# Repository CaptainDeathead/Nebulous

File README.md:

# Nebulous

Nebulous is a retro console system powered by a Raspberry Pi. Designed for both nostalgia and innovation, it offers a unique blend of custom hardware and software to deliver an exciting multiplayer gaming experience.

## Features

- **Custom Controllers**: Nebulous supports up to 4 controllers for multiplayer gaming.
- **SD Card Cartridges**: Games are loaded via SD card cartridges, offering a retro game-swapping experience.
- **3D Printed Shell**: The physical console is encased in a sleek and durable 3D-printed shell.
- **Custom Games**: Includes a variety of games designed specifically for Nebulous (see the list below).
- **NES Game Support**: Play classic `.nes` files for old NES games.

## Custom Games

The `games` directory contains the following games created specifically for Nebulous using Pygame:

- **Caliby**: A calibration tool for testing controllers with the Nebulous.
- **Meteors**: A 4-player Asteroids clone.
- **Pong**: The classic Pong game.
- **Shape Royale**: A class-based battle royale where you play as 2D shapes.
- **Snither**: A multiplayer merge of Slither.io and classic Snake.
- **Tetris**: A 4-player version of the timeless Tetris game.

## Design Files

All files related to the physical design of Nebulous are located in the `/design` directory, including:

- **3D Printing Files**: Models for the Nebulous shell.
- **Controller PCB Designs**: Schematics and layouts for custom controllers.
- **Wiring Designs**: Diagrams and plans for wiring the console, controllers, and other components.

## How It Works

- **Without Cartridge**: If no game cartridge is inserted, the console will prompt you to insert one.
- **With Cartridge**: When a cartridge is inserted, the console attempts to load and play the game.

## Getting Started

1. **Hardware Setup**:
   - Assemble the 3D-printed case using files from the `/design` directory.
   - Connect up to 4 custom controllers using the provided PCB and wiring designs.
   - Insert an SD card cartridge containing your desired game.

2. **Software Setup**:
   - Clone the repository:
     ```bash
     git clone https://github.com/CaptainDeathead/Nebulous.git
     ```
   - Navigate to the `rpi-install` directory and run the `install.sh` script to set up the console:
     ```bash
     cd Nebulous/rpi-install
     ./install.sh
     ```

3. **Running Games**:
   - Insert a game cartridge to start playing.
   - Alternatively, load a `.nes` file for older NES games.

## Contributing

Contributions are welcome! Feel free to submit pull requests or open issues for bug reports and feature suggestions.

## License

This project is licensed under the MIT License - see the [LICENSE](LICENSE) file for details.

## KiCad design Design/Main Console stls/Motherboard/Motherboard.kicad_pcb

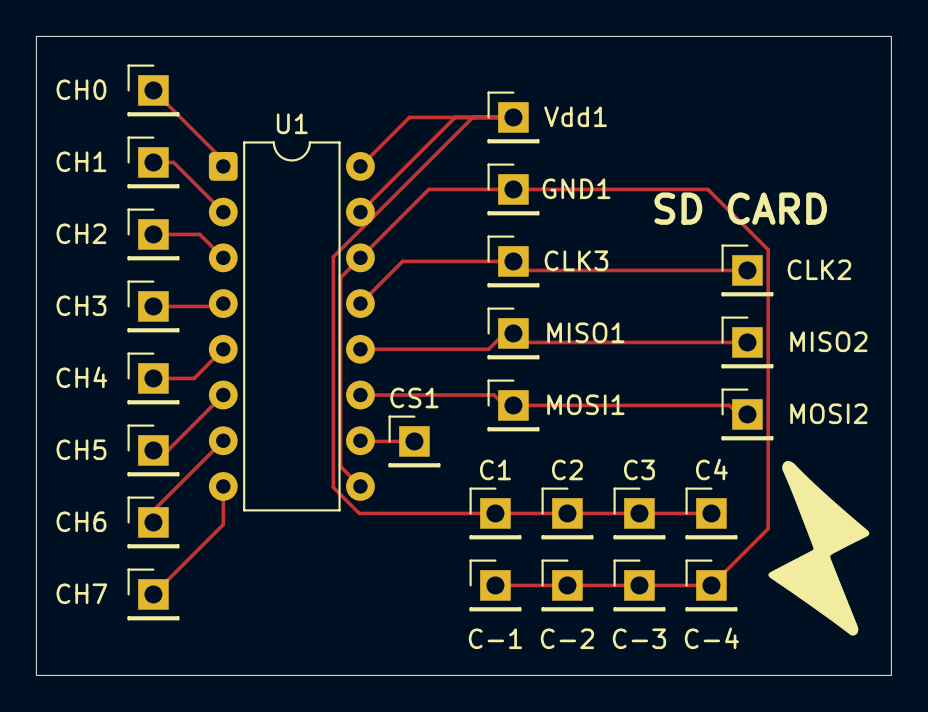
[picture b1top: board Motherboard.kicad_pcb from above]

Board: 2 copper layers, 47.5 x 35.5 mm, 26 parts (0 on the bottom side), 14 nets.

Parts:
C1, C2, C3, C4: TestPoint; PinHeader_1x01_P2.54mm_Vertical
C-1, C-2, C-3, C-4: TestPoint; PinHeader_1x01_P2.54mm_Vertical
CH0, CH1, CH2, CH3, CH4, CH5, CH6, CH7: TestPoint; PinHeader_1x01_P2.54mm_Vertical
CLK2, CLK3: TestPoint; PinHeader_1x01_P2.54mm_Vertical
CS1: TestPoint; PinHeader_1x01_P2.54mm_Vertical
GND1: TestPoint; PinHeader_1x01_P2.54mm_Vertical
MISO1, MISO2: TestPoint; PinHeader_1x01_P2.54mm_Vertical
MOSI1, MOSI2: TestPoint; PinHeader_1x01_P2.54mm_Vertical
U1: MCP3008; DIP-16_W7.62mm
Vdd1: TestPoint; PinHeader_1x01_P2.54mm_Vertical

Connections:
unnamed: C-1.1, C-2.1, C-3.1, C-4.1, GND1.1, U1.9 (DGND), U1.14 (AGND)
unnamed: CH0.1, U1.1 (CH0)
unnamed: CH1.1, U1.2 (CH1)
unnamed: CH2.1, U1.3 (CH2)
unnamed: CH3.1, U1.4 (CH3)
unnamed: CH4.1, U1.5 (CH4)
unnamed: CH5.1, U1.6 (CH5)
unnamed: CH6.1, U1.7 (CH6)
unnamed: CH7.1, U1.8 (CH7)
unnamed: CLK2.1, CLK3.1, U1.13 (CLK)
unnamed: MOSI1.1, MOSI2.1, U1.11 (Din)
unnamed: MISO1.1, MISO2.1, U1.12 (Dout)
unnamed: C1.1, C2.1, C3.1, C4.1, U1.15 (Vref), U1.16 (Vdd), Vdd1.1
unnamed: CS1.1, U1.10 (~CS/SHDN)

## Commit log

2025-03-06 Basic setup script for raspberry pis
2025-03-06 Basic file structure
2025-03-06 Basic snake class
2025-03-06 Basic splitscreen management
2025-03-06 Began work on main menu
2025-03-07 Massive changes! Basic Console SDK
2025-03-07 Updated Games/ to be loaded with Console SDK
2025-03-08 Fixed bug to do with self.enter_cartridge_surf.height also added some files for upcoming additions
2025-03-09 Basic changes to console, but Snither nearly done
2025-03-09 pygame-ce has .height as a property of surfaces
2025-03-09 Fixed importing in cartridge_loader
2025-03-09 Added duel SPI support
2025-03-09 added some stuff to meteors
2025-03-10 Added sound and some console stuff
2025-03-10 Changes to install script
2025-03-10 Fixed MCP3008 channels
2025-03-10 Going back to old controller MCP3008 instance code
2025-03-10 Pigpiod backend rather than gpiozero default
2025-03-10 Add testing = False to cartridge_loader
2025-03-10 Fixes to gpio
2025-03-10 Override testing arg in cartridge_loader
2025-03-10 Fix no self argument in controller.py
2025-03-10 Fixed install script run dir
2025-03-10 Fix typo in install script
2025-03-11 Hopefully working controller events
2025-03-11 Controller events using correct class
2025-03-11 Snakes can now have controller input
2025-03-11 Add controller event regestry logic
2025-03-11 Set log level to debug
2025-03-15 make meteors launchable at least
2025-03-15 Made bullets work
2025-03-15 added nothing
2025-03-15 Added some games and fixed ai for snither
2025-03-15 Fixed grow and win conditions
2025-03-15 Fixed space bug with timeout
2025-03-15 Bug fixes + infinite mode snither
2025-03-15 Quit infinite mode
2025-03-15 Made asteroids playable cooked meth
2025-03-15 Began work on shape royale
2025-03-16 Setting up classes for Shape Royale
2025-03-16 Shape royale gameplay pretty much done, VERY UNOPTIMISED OML
2025-03-19 Basic zone improvements to shape royale
2025-03-20 Possible sd card cartridges
2025-03-20 Display=0
2025-03-20 Testing = False
2025-03-20 Cartridge loader fix
2025-03-20 SD Fixes
2025-03-21 SD block reading better maybe?
2025-03-21 Added snither xz again
2025-03-21 Added bytes to len of xz
2025-03-21 xz_length int convertion
2025-03-21 Add fileobj arg to xz unzip
2025-03-21 SD Debugging
2025-03-21 Fix xz length
2025-03-22 Cartridges?
2025-03-23 Shape Royale save zone visible
2025-03-24 Added Design/ files
2025-03-25 Shape Royale balancing and ability fixes
2025-03-25 Added controller input detection and testing mode
2025-03-26 WORKING CONTROLLERSgit add ..!
2025-03-26 GPIO config pin for controllers
2025-03-26 GPIO fix
2025-03-26 Debugging for GPIO pin
2025-03-26 GPIO pin pull_down
2025-03-26 Caliby darkens unplugged controllers
2025-03-26 Working controller switching
2025-03-27 Moved snither input
2025-03-28 Large changes to design directory
2025-03-28 added gerber file for controller + added method
2025-03-29 Added seperating metoers
2025-03-29 Made meteors more like asteroids
2025-03-29 did something? i forgot
2025-03-30 minor changes
2025-03-30 tiny commit with slightly borked method
2025-03-31 Added Trash mode to Meteors for performance
2025-03-31 restore progress
2025-03-31 thing
2025-03-31 minor changes to multiplayer
2025-04-01 Cartridges done, Console IO done. controllers ghosting lots (physical)
2025-04-01 Bug fixes
2025-04-06 Pong; Game crash screen; Extra console info
2025-04-07 Moved cartridge read check
2025-04-07 Less controller polling
2025-04-07 Fix cartridge unload check
2025-04-09 made variable player amounts
2025-04-09 slight changes
2025-04-09 ufo functionality
2025-04-09 almost done - ready to merge
2025-04-11 Working on open day
2025-04-11 Added --flash arg, removed controller update thread, fixed snither main menu spam inputs
2025-04-11 completed meteors
2025-04-11 Basic improvements
2025-04-11 Basic uinput controllers
2026-01-11 Added nes??
2026-01-11 Snither main menu controller plug toggle
2026-01-12 Made v1 motherboard
